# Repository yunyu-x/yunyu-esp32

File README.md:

# yunyu-esp32: 灵伴·悄悄 (LingBuddy) 物理具身智能伴侣与 ESP32 开源硬件套件

<div align="center">

**全栈独立、开箱即用的随身/桌面具身 AI 伴侣、微信小程序终端、Meta Muse Gadgets 生态与开源机器人硬件基座**  
*Full-Stack Independent Physical AI Voice Companion, WeChat Mini-Program Suite, Meta Muse Gadgets & Embedded Robotics*

[Release Notes v1.1.0](./docs/RELEASE_NOTES_v1.1.0.md) | [English](#english-summary) | [核心特性](#-核心特性-key-features) | [系统架构](#-系统架构-architecture) | [六大公理](#-不可违背的六大工程公理-the-6-constitutional-axioms) | [工程知识库](#-项目工程知识库-project-engineering-documentation) | [技能扩展](#-标准化技能扩展-standardized-skills) | [快速起步](#-快速起步-quick-start)

</div>

---

## 📖 项目简介 (Overview)

`yunyu-esp32` 是一个**完全独立自洽的物理具身 AI 伴侣与开源硬件生态工程**。本项目将前沿大语言模型与多模态情感计算深度融入嵌入式物理实体，构建了涵盖**嵌入式固件、微信小程序客户端、桌面 Web 伴侣、Meta Muse 具身代理接入、开源机器人机电控制及严格工程测试**的全栈闭环：

1. **灵伴·悄悄 (LingBuddy / Qiaoqiao) 嵌入式固件 (`firmware/m5sticks3_buddy`)**：
   运行在 M5Stack StickS3（ESP32-S3-PICO-1，8MB Flash + 8MB PSRAM）硬件底座上。内置离线声学唤醒词「悄悄」匹配引擎、阿里云百炼实时语音大模型全双工流式问答、正面按键 A 毫秒级物理打断（Barge-In）、12 种迪士尼拟态矢量微表情与 Tamagotchi 亲密度系统、8 轮长程记忆滑动压缩与 NVS 持久化、PSRAM 135×240 零撕裂双缓冲显存、异步 BLE 指令队列以及网络多态徽章。
2. **微信小程序端产品套件 (`wechat_miniprogram/`)**：
   秉持 Apple Human Interface Guidelines (HIG) 原生极简美学打造。涵盖 4 大核心 Tab（首页动态表情与心声、投喂互动中心、心声日记流、设置与配网面板）；支持蓝牙 BLE NUS 多包流式组包通讯、双通道配网（常规宽带 Wi-Fi 与手机共享移动热点自适应切换）、热点流量配额监控与超额自动熔断防护、DPR 自适应 `<avatar-canvas>` 动态微表情渲染、Taptic 触觉反馈震动以及离线优先本地存储。
3. **桌面与 Web 伴侣控制台 (`web/` & `scripts/`)**：
   提供基于 Web Bluetooth API 的隔空投喂中心 (`web/lingbuddy_companion.html`)、双向音频测试网关、以及两级语义向量检索记忆知识库 (`scripts/lingbuddy_vector_store.py`)。
4. **Meta Muse Gadgets 生态原生接入 (`external_repos/muse-gadget-sdk`, `include/muse_gadget_client.h`, Doc 31)**：
   深度研学并接入 Meta 官方开源的 Muse Gadgets 框架。通过 Noise_XX 全双工加密隧道和 Home Link 建立与云端 Muse Secure VM 的持久连接，支持 Push-to-Talk 24kHz 流式交互与本地具身 RPC 控制。
5. **开源机器人硬件扩展 (`microduck/` & `hardware/`)**：
   包含 MicroDuck 双足走路鸭机器人（基于 ESP32 的 CPG 步态引擎与舵机标定系统）、以及灵方微型机器人主控 PCBA v2.0（4层沉金 PCB、SPICE 多回路严苛仿真验证）。
6. **自动化工程测试与持续集成 (`tests/`)**：
   内置 100 项覆盖声学唤醒、音频防破音限幅、微表情动力学、BLE NUS 分包重组、热点配额熔断、驱动 Hub、硬件自测的自动化回归测试，100% 绿色通过。

---

## 🚀 核心特性 (Key Features)

### 1. 全双工大模型语音交互与离线唤醒
- **离线声学唤醒词「悄悄」**：基于板载 MEMS 硅麦 + ES8311 音频前端，毫秒级快速声学特征匹配，抗噪免疫；
- **阿里云百炼实时大模型 (DashScope Realtime WSS)**：16kHz 16-bit Mono PCM 双向双工流式传输，低延迟语音合成回放（AW8737 功放驱动）；
- **物理打断 (Barge-In)**：语音回放过程中随时按下正面按键 A，瞬时中断服务端合成与硬件回放，即刻重置拾音。

### 2. 迪士尼拟态微表情与情感动力学系统 (Tamagotchi Engine)
- **12 种拟态微表情**：涵盖开心、好奇、思考、眨眼、睡觉、惊讶、撒娇等细腻情感，具备凝视追踪与眨眼物理衰减阻尼；
- **Tamagotchi 亲密度系统**：记录投喂、抚摸与对话频次，数值随时间平滑演化，驱动微表情与交互心声动态进阶；
- **PSRAM 显存零撕裂双缓冲 (Axiom 3)**：开辟 135×240 @ 16-bit RGB565 精灵显存画布（仅占 64.8KB PSRAM），离线合成后经 SPI DMA 单次原子性推送，彻底根除 15Hz 物理闪烁与背光撕裂。

### 3. 跨端自适应通讯与双通道安全配网
- **BLE Nordic UART Service (NUS)**：广播合规 30 字节，特征值支持高速无应答写入；
- **双通道智能配网**：
  - **常规宽带 Wi-Fi 模式**：局域网高速通道，设备徽章亮绿底 **"WiFi"**；
  - **手机共享热点模式**：顶部与设备端徽章显示暖橙底 **"HOT"**，小程序实时统计已用流量 MB，支持配额设定与超额硬件级断网熔断保护；
  - **断网警示**：网络异常时设备显示亮红底 **"!NET"**。
- **防截断多包分片流 (Axiom 6)**：长文本与记忆 JSON 经自适应分片流传输，内置 `safeTruncateUtf8` 字符级边界保护器，杜绝非法字节导致的 WebSocket 1007 协议违规或解析异常。

### 4. Apple HIG 人文美学微信小程序
- **iOS 原生质感**：纯黑背景 (`#000000`)、层级卡片 (`#1C1C1E` / `#2C2C2E`)、SF Pro / PingFang 规范排版、0.5px 极细微边框；
- **四 Tab 完整产品布局**：首页微表情、隔空投喂甜品货架、Notes 风格心声随笔、iOS 设置分组配网；
- **微信上线保障**：内置离线仿真模式（Demo Mode）与硬件视频指引，轻松应对微信平台审核。

---

## 📐 系统架构 (Architecture)

```mermaid
flowchart TD
    subgraph Clients["调测与交互客户端 (Clients)"]
        WeChat["微信小程序 (WeChat Mini-Program)<br/>Apple HIG 美学 / 4-Tab / 热点流量监控"]
        WebDash["Web 蓝牙/局域网伴侣控制台<br/>隔空投喂 / 向量检索 / 音频调试"]
        MetaMuse["Meta Muse 代理大脑<br/>Muse Secure VM / Noise_XX Home Link"]
        Desktop["PC 桌面开发终端<br/>PlatformIO / 串口 COM3 诊断 / Pytest"]
    end

    subgraph StickS3["StickS3 物理伴侣 (代号「悄悄」) 核心中枢"]
        direction TB
        subgraph NetLayer["通信与协议解耦层 (Axiom 2 & 6)"]
            BLE_NUS["BLE NUS (0xFFB0)<br/>自旋锁 micro-queue 入队"]
            WiFi_Hotspot["双通道网络引擎<br/>宽带 WiFi / 手机热点 HOT / 流量熔断"]
            MuseClient["Meta Muse Gadget 客户端<br/>Noise_XX 隧道 / 串口 Hatch"]
            HttpServer["轻量级 REST API<br/>/api/pet/status /api/wifi/config"]
        end
        
        subgraph CoreTasks["FreeRTOS 核心任务调度"]
            LoopTask["主循环 loopTask (16KB+ 栈)<br/>StickS3BLESync::update() 消费指令"]
            AudioTask["双工音频任务 audioTask (6KB 栈)<br/>离线唤醒 + DashScope PCM 流"]
            AvatarTask["微表情与亲密度计算<br/>12 种拟态动作 + 物理水准仪"]
        end

        subgraph DisplaySub["显存渲染子系统 (Axiom 3)"]
            Canvas["PSRAM 双缓冲显存画布<br/>LGFX_Sprite (135x240 @ 16-bit RGB565)"]
            LCD["ST7789v2 1.14' 物理屏幕<br/>SPI DMA 单次原子推送 (零撕裂)"]
            Canvas -->|DMA Push| LCD
        end

        AudioSub["音频子系统 (PSRAM 320KB)<br/>MEMS 硅麦 + ES8311 + AW8737 功放"]
        MemoryStore["长程记忆引擎<br/>8 轮两级窗口压缩 + NVS 持久化"]
    end

    subgraph HardwareExt["具身与硬件扩展 (Embodied Hardware)"]
        MicroDuck["MicroDuck 双足走路鸭机器人<br/>ESP32 CPG 步态引擎 / 舵机校准"]
        LingCube["灵方微型机器人主控 PCBA v2.0<br/>4层沉金板 / DRV8833 / EPM 磁吸"]
    end

    WeChat -->|BLE NUS 0xFFB4 / 手机热点| BLE_NUS
    WebDash -->|Web Bluetooth / HTTP| BLE_NUS
    WebDash -->|Wi-Fi SoftAP / HTTP 80| HttpServer
    MetaMuse -->|Home Link / HTTP RPC| MuseClient
    Desktop -->|串口 COM3 / 烧录| StickS3

    NetLayer -->|微栈入队| CoreTasks
    CoreTasks --> DisplaySub
    CoreTasks <--> AudioSub
    CoreTasks <--> MemoryStore

    StickS3 -.->|HIL 步态遥控| MicroDuck
    StickS3 -.->|HIL 地面调测| LingCube
```

---

## ⚖️ 不可违背的六大工程公理 (The 6 Constitutional Axioms)

依据 [`docs/30_PROJECT_AXIOMS_AND_HANDOVER.md`](./docs/30_PROJECT_AXIOMS_AND_HANDOVER.md)，在 `yunyu-esp32` 的持续演进中，**以下六大公理为不可违背的最高工程基石**：

1. **【公理一：真实硬件烧录验证公理】(Strict Hardware Verification Law)**  
   固件改动绝不能停留在“代码编写完成”或“本地编译通过”，必须经由 PlatformIO 烧录至真实连接的物理硬件（`COM3`），触发 RTS/DTR 硬件级硬重启，实测阅读 10~15 秒串口日志确认自检全项通过。
2. **【公理二：中断与通讯协议栈异步解耦公理】(Interrupt & Protocol Task Decoupling Law)**  
   在 ESP-IDF 底层任务（特别是堆栈仅 3KB 的 `BTC_TASK`）中严禁执行 NVS 读写、Wi-Fi 切换或阻塞计算；所有下发指令仅在自旋锁临界区向微栈队列入队，并在拥有 16KB+ 栈空间的 `loopTask` 中异步消费。
3. **【公理三：显存零撕裂双缓冲物理公理】(Zero-Tear Double-Buffering Law)**  
   杜绝物理屏直写清屏。必须利用 8MB PSRAM 开辟 135×240 精灵画布（`LGFX_Sprite`），所有汉字、微表情与水准仪在显存中无缝合成后经 SPI DMA 单次原子推送，彻底消除频闪。
4. **【公理四：网络模式显式区分与端到端一致性公理】(Explicit Network Mode & Coherence Law)**  
   严格区分手机热点（橙色 "HOT" / 流量监控看板与熔断保护）与常规宽带（绿色 "WiFi"），断网亮红底 "!NET"；小程序主页与设置页数据源 100% 一致。
5. **【公理五：零功能回退与渐进加固公理】(Non-Regression & Progressive Hardening Law)**  
   任何新增功能不得导致已有基线特性（离线唤醒词「悄悄」、阿里百炼流式语音、按键打断、12种微表情、8轮记忆压缩、I2C互斥锁）发生任何劣化。
6. **【公理六：跨端自适应协议与防截断编码公理】(Adaptive Multi-Chunk & Robust Encoding Law)**  
   跨端通信长文本必须支持多包分片流与接收端组包拼帧；文本截断必须使用字符级算法（`safeTruncateUtf8`），严禁跨字节撕裂导致解析崩溃或 WebSocket 1007 协议违规。

---

## ⚡ 硬件定义与引脚映射 (Pinout Specifications)

### M5Stack StickS3 板载核心外设映射

| 外设模块 | 核心芯片 / 组件 | ESP32-S3 GPIO 引脚 | 驱动方式与通信协议 | 说明 |
| :--- | :--- | :--- | :--- | :--- |
| **电源门控** | M5PM1 PMIC | I2C (SDA: G10, SCL: G9) | I2C Addr `0x6E` | GPIO2: LCD 3.3V, GPIO3: 功放使能 |
| **正面按键 A** | 主功能实体按键 | **GPIO 11** | 内部上拉输入 | 语音物理打断 (Barge-In) / 录音触发 |
| **侧面按键 B** | 辅助控制实体按键 | **GPIO 12** | 内部上拉输入 | 页面轮换与辅助功能切换 |
| **彩色屏幕** | ST7789v2 1.14" LCD | SPI3 (SCLK: G17, MOSI: G18, DC: G15, CS: G14, RST: G21) | SPI (27MHz DMA) | 135 × 240 分辨率，PSRAM 双缓冲显存 |
| **6轴姿态计** | Bosch BMI270 | I2C (SDA: G10, SCL: G9) | I2C Addr `0x69` | 姿态角感应与动态水准球平衡算法 |
| **音频前端** | ES8311 + AW8737 PA | I2S0 (LRCK: G7, BCLK: G8, DOUT: G6, DIN: G5) | I2S (16kHz 16bit Mono) | 板载 MEMS 硅麦采集 + 喇叭流式回放 |
| **外扩动力接口** | Grove 4-Pin 接口 | GPIO 1 / GPIO 2, 5V, GND | M5PM1 门控 5V | 外接 MicroDuck 舵机或机器人 HIL 调测 |

---

## 📚 项目工程知识库 (Project Engineering Documentation)

本项目建立了完备、专业的技术文档体系，全部文档归档于 [`docs/`](./docs/)：

| 专案分类 | 文档名称与索引 | 核心论证与工程规范 |
| :--- | :--- | :--- |
| **最高工程基石** | [**30_PROJECT_AXIOMS_AND_HANDOVER.md**](./docs/30_PROJECT_AXIOMS_AND_HANDOVER.md) | 六大不可违背工程公理、实机监控基线、全套工具链验证命令与会话交接指南 |
| **提示词标准库** | [**AGENT_CONTINUATION_PROMPTS.md**](./docs/AGENT_CONTINUATION_PROMPTS.md) | 跨生命周期 AI Agent 通用母版、细分研发方向（审批终端/地面台/菜单）提示词模板 |
| **微信小程序端** | [**28_M5StickS3微信小程序对接架构与通信协议工程指南.md**](./docs/28_M5StickS3微信小程序对接架构与通信协议工程指南.md)<br/>[**29_微信小程序与移动端研发交接指南_HANDOVER_MOBILE.md**](./docs/29_微信小程序与移动端研发交接指南_HANDOVER_MOBILE.md) | 小程序 4-Tab 完整架构、BLE NUS 分包重组、热点配额监控熔断、上线审核攻略 |
| **Meta Muse 接入** | [**31_Meta_Muse_Gadgets微型自重构机器人与物理伴侣全栈接入方案与工程实施详案.md**](./docs/31_Meta_Muse_Gadgets微型自重构机器人与物理伴侣全栈接入方案与工程实施详案.md) | Meta 2026-10-02 开源 `muse-gadget-sdk` 研学、Noise_XX 隧道、具身技能标准与实施详案 |
| **伴侣与表情架构** | [**27_基于MuseCharm哲学的M5StickS3灵宠伴侣软硬件架构与工程论证大案.md**](./docs/27_基于MuseCharm哲学的M5StickS3灵宠伴侣软硬件架构与工程论证大案.md)<br/>[**27_StickS3物理伴侣全流程对话开发实录与教学手册.md**](./docs/27_StickS3物理伴侣全流程对话开发实录与教学手册.md) | 迪士尼微表情动力学、Tamagotchi 亲密度系统、长程记忆压缩与对话实录教程 |
| **硬件与调测基线** | [**01_StickS3_Hardware_and_Bringup_Guide.md**](./docs/01_StickS3_Hardware_and_Bringup_Guide.md)<br/>[**03_StickS3_Three_Schemes_Verification.md**](./docs/03_StickS3_Three_Schemes_Verification.md)<br/>[**25_M5Stack_StickS3物理伴侣与地面调测终端开发全流程及三方案验证详案.md**](./docs/25_M5Stack_StickS3物理伴侣与地面调测终端开发全流程及三方案验证详案.md) | M5StickS3 硬件上电流程、三大方案（M5Burner / PlatformIO / Claude Buddy）全面验证 |
| **双向语音与资源** | [**HANDOVER_VOICE_DIALOGUE_AND_RESOURCE_MANAGEMENT.md**](./docs/HANDOVER_VOICE_DIALOGUE_AND_RESOURCE_MANAGEMENT.md)<br/>[**RELEASE_NOTES_v1.0.0.md**](./docs/RELEASE_NOTES_v1.0.0.md) | 百炼实时语音流、双向音频协议、内存防溢出与 v1.0.0 稳定生产基线发布记录 |

---

## 🛠️ 标准化技能扩展 (Standardized Skills)

项目所有专属专业技能均统一梳理并保存在根目录 `skills/` 下，已配置 `.agents/skills.json` 支持 Antigravity 全自动化识别与调度：

1. **[skills/lingbuddy-firmware-ops/](./skills/lingbuddy-firmware-ops/SKILL.md)**：  
   StickS3 嵌入式固件编译、极速烧录（`COM3`）、硬重启检验与六大公理违规审计技能；
2. **[skills/wechat-miniprogram-companion/](./skills/wechat-miniprogram-companion/SKILL.md)**：  
   微信小程序伴侣研发、Apple HIG 视觉规范审查、BLE NUS 多包通信协议、双通道配网与发布上线技能；
3. **[skills/muse-gadget-companion/](./skills/muse-gadget-companion/SKILL.md)**：  
   Meta Muse Gadgets 接入与具身技能管理（Noise_XX 隧道、Home Link 穿透、Push-to-Talk 24kHz 流）；
4. **[skills/public-service-tunnel/](./skills/public-service-tunnel/SKILL.md)**：  
   本地伴侣控制台与 Web 预览在线穿透管理技能（ngrok、Cloudflare Quick Tunnel 自适应容灾切换）；
5. **[skills/document-content-verifier/](./skills/document-content-verifier/SKILL.md)**：  
   第一性原理与公理化文档内容交叉复核技能（自然科学公理、量纲齐次性、多模态交付）；
6. **[skills/open-source-repo-analyzer/](./skills/open-source-repo-analyzer/SKILL.md)**：  
   自主开源项目研学、AST 源码分析与跨项目接口适配器生成技能；
7. **[skills/pcb-design-verifier/](./skills/pcb-design-verifier/SKILL.md)**：  
   KiCad 原理图/PCB 审查与多回路 SPICE 瞬态电路仿真技能；
8. **[skills/gadget-lingcube-msrr/](./skills/gadget-lingcube-msrr/SKILL.md)** & **[skills/gadget-lingmatrix-sim/](./skills/gadget-lingmatrix-sim/SKILL.md)**：  
   Meta Muse 具身物理机器人控制与数字孪生仿真技能。

---

## 🛠️ 快速起步 (Quick Start)

### 1. 环境准备与依赖安装
```bash
# 1. 安装 Python 核心依赖 (包含 platformio, pytest, bleak, numpy 等)
pip install -r requirements.txt

# 2. 安装小程序端构建依赖 (若需运行微信开发者工具自动化)
npm install
```

### 2. 固件编译与真实硬件烧录 (践行公理一)
```bash
# 本地编译固件
python -m platformio run -e m5sticks3_buddy

# 烧录固件至物理硬件 (本地串口 COM3)
python -m platformio run -e m5sticks3_buddy -t upload

# 触发 RTS/DTR 硬件级硬重启并读取实时串口自检日志 (运行 10~15 秒)
python -c "import serial, time; ser = serial.Serial('COM3', 115200, timeout=1); ser.setDTR(False); ser.setRTS(True); time.sleep(0.1); ser.setRTS(False); time.sleep(0.2); start = time.time(); [print(ser.readline().decode('utf-8', errors='replace').strip()) for _ in iter(lambda: ser.readline() if time.time()-start < 10 else None, None)]; ser.close()"
```

### 3. 执行全套 100 项自动化回归测试
```bash
pytest tests/ -v
```
*(100 项声学唤醒、百炼双工、音频防破音限幅、微表情动力学、BLE多包拼帧、热点配额熔断、驱动 Hub、硬件自测全部通过)*

### 4. 微信小程序开发与预览
1. 打开**微信开发者工具**；
2. 导入项目目录：`D:\workspace\code\yunyu-esp32\wechat_miniprogram`；
3. 输入测试 AppID 或使用已有的小程序账号；
4. 即可在模拟器中体验暗黑 Apple HIG 美学界面、4 大 Tab、微表情渲染与仿真交互模式；连接真实 StickS3 时自动开启 BLE NUS 双向通信。

### 5. 桌面 Web 蓝牙伴侣与向量知识库
```bash
# 启动本地伴侣控制台 Web 服务
python scripts/lingbuddy_companion.py
# 浏览器访问: http://127.0.0.1:8000 (支持 Chrome / Edge Web Bluetooth 直连)

# 启动向量记忆知识库查询
python scripts/lingbuddy_vector_store.py
```

---

## 📂 仓库目录结构 (Directory Structure)

```
yunyu-esp32/
├── .agents/                       # Antigravity Agent 技能索引配置 (skills.json)
├── .github/                       # GitHub Actions CI 流水线
├── docs/                          # 项目最高公理、工程交接、提示词库与全套技术详案 (Docs 01~31)
├── firmware/
│   └── m5sticks3_buddy/           # StickS3 物理伴侣与双模地面调测台工程 (PlatformIO)
│       ├── include/               # 离线唤醒、音频驱动、微表情、BLE同步、百炼Client、MuseClient
│       ├── src/                   # main.cpp, sticks3_hal.cpp, buddy_protocol.cpp
│       └── platformio.ini         # PlatformIO 编译构建配置
├── wechat_miniprogram/            # 微信小程序端 4-Tab 完整产品套件
│   ├── pages/                     # index (首页), feed (投喂), diary (日记), settings (设置配网)
│   ├── components/avatar-canvas/  # DPR 自适应矢量微表情渲染组件
│   ├── utils/                     # BLE 通信、Wi-Fi/热点管理、触觉反馈、离线存储、加密防护
│   └── assets/tabbar/             # 苹果暗黑高保真 TabBar 图标资产
├── web/
│   └── lingbuddy_companion.html   # Web Bluetooth / Wi-Fi 隔空投喂伴侣控制台
├── external_repos/
│   └── muse-gadget-sdk/           # Meta Muse Gadgets 官方开源硬件与通信 SDK
├── microduck/                     # MicroDuck 双足走路鸭机器人机电步态工程
├── hardware/                      # 灵方微型机器人主控 PCBA v2.0 与硬件设计资产
├── scripts/                       # 自动化点亮代理、向量检索、对话压测、音频自测脚本
├── skills/                        # 8 项标准化 Antigravity 专属技能扩展
├── tests/                         # 100 项全自动化回归测试套件 (Pytest)
├── package.json                   # 小程序与前端构建工具链配置
├── pyproject.toml                 # 现代化 Python 包元数据与 pytest 配置
├── requirements.txt               # Python 运行与构建依赖
├── CONTRIBUTING.md                # 代码贡献与工程准则
├── LICENSE                        # Apache License 2.0 开源协议
└── README.md                      # 本文档
```

---

## 📄 开源许可证 (License)

本项目遵循 [Apache License 2.0](./LICENSE) 协议开源。软件源码、固件代码、微信小程序套件及硬件工程设计均保障商业友好与学术研究自由。

---

<div id="english-summary">

### English Summary

`yunyu-esp32` is a fully decoupled, standalone open-source physical AI voice companion and embodied robotics hardware ecosystem.

**Core Highlights**:
- **LingBuddy (悄悄) Companion Firmware**: Running on M5Stack StickS3 (ESP32-S3), featuring offline acoustic wakeword "悄悄", Alibaba Bailian DashScope Realtime full-duplex voice streaming, physical button barge-in, 12 Disney-inspired parametric avatar emotions, Tamagotchi intimacy engine, 8-turn long-horizon memory compaction, zero-tear PSRAM double-buffering (Axiom 3), and async spinlock BLE queue (Axiom 2).
- **WeChat Mini-Program Product Suite**: Built with Apple Human Interface Guidelines (HIG) aesthetic, offering 4 primary tabs (Avatar & Thoughts, Feeding Center, Heartfelt Diary, and Network Settings), BLE Nordic UART Service multi-chunk streaming, dual-channel network provisioning (broadband Wi-Fi + mobile hotspot with quota cutoff protection), DPR-aware `<avatar-canvas>`, and haptic feedback.
- **Meta Muse Gadgets Ecosystem Integration**: Native compliance with Meta's open-source Muse Gadget SDK, supporting Noise_XX encrypted Home Link tunneling, Push-to-Talk 24kHz audio, and embodied robotics skill dispatching.
- **MicroDuck Bipedal Robotics**: CPG locomotion gait controller, servo calibration, and hardware kinematics.
- **6 Constitutional Axioms**: Strict adherence to hardware-verified releases, task decoupling, anti-flicker double-buffering, network coherence, non-regression, and safe Unicode-boundary encoding.

</div>

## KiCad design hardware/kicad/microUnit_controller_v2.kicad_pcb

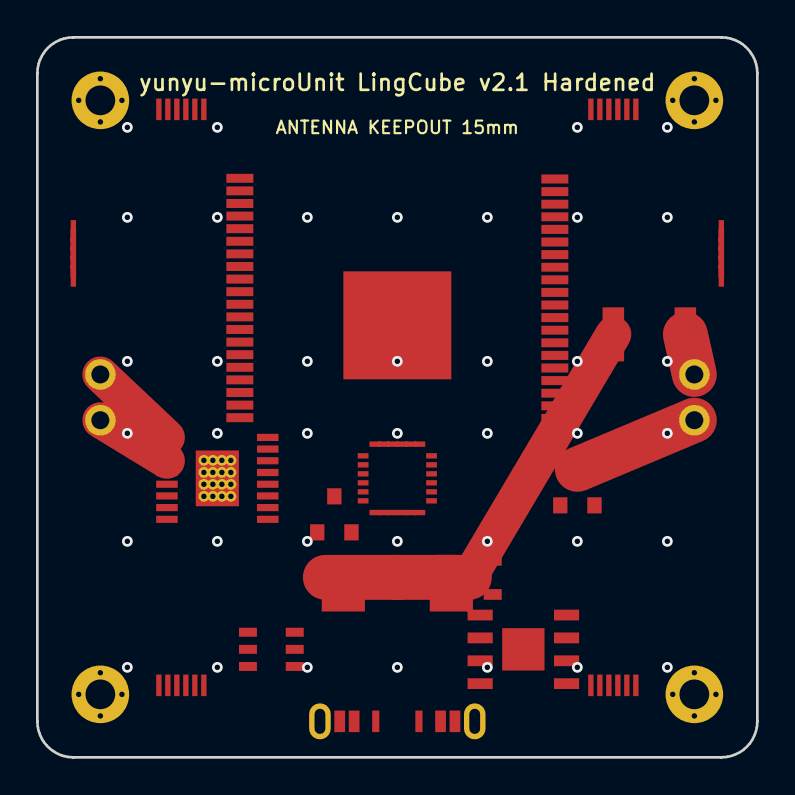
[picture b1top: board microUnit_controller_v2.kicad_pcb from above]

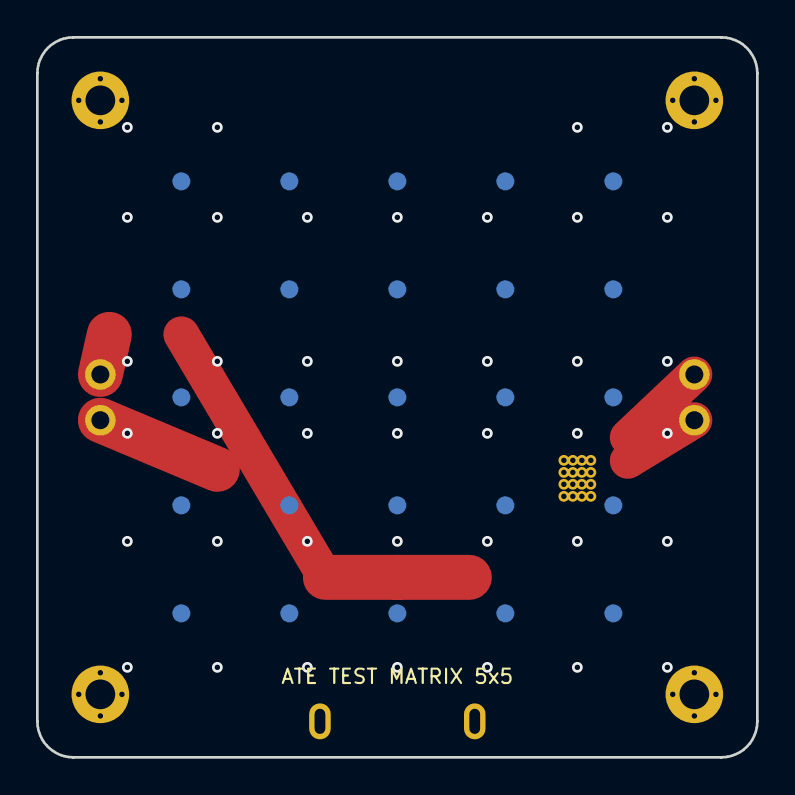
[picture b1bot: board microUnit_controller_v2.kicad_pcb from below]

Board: 4 copper layers, 40.0 x 40.0 mm, 48 parts (25 on the bottom side), 15 nets.

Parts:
C1: 470uF POSCAP; CP_EIA-7343-31_Kemet-D
F1: 1812L150PR_1.5A; Fuse_1812_4532Metric
H1, H2, H3, H4: M1.6_GND_MOUNT; MountingHole_1.65mm_M1.6_Pad_ViaStitched
J2: MOTOR_OUT; PinHeader_1x02_P2.54mm_Vertical
J3: EPM_COIL_OUT; PinHeader_1x02_P2.54mm_Vertical
J4: FPC_FACE_POS_X; Hirose_FH12-6S-0.5SH_1x06-1MP_P0.50mm_Horizontal
J5: FPC_FACE_NEG_X; Hirose_FH12-6S-0.5SH_1x06-1MP_P0.50mm_Horizontal
J6: FPC_FACE_POS_Y; Hirose_FH12-6S-0.5SH_1x06-1MP_P0.50mm_Horizontal
J7: FPC_FACE_NEG_Y; Hirose_FH12-6S-0.5SH_1x06-1MP_P0.50mm_Horizontal
J8: FPC_FACE_POS_Z; Hirose_FH12-6S-0.5SH_1x06-1MP_P0.50mm_Horizontal
J9: FPC_FACE_NEG_Z; Hirose_FH12-6S-0.5SH_1x06-1MP_P0.50mm_Horizontal
J_USB: TYPE-C-16P; USB_C_Receptacle_GCT_USB4105-xx-A_16P_TopMnt_Horizontal
Q1: AO3400A; SOT-23
Q4: AO3401A_IMU_SW; SOT-23
TP1: TP_VBAT_CELL; TestPoint_Pad_D1.0mm_OD1.6mm
TP2: TP_VBAT_SW; TestPoint_Pad_D1.0mm_OD1.6mm
TP3: TP_VCC_3V3; TestPoint_Pad_D1.0mm_OD1.6mm
TP4: TP_GND; TestPoint_Pad_D1.0mm_OD1.6mm
TP5: TP_VBUS_5V; TestPoint_Pad_D1.0mm_OD1.6mm
TP6: TP_EN; TestPoint_Pad_D1.0mm_OD1.6mm
TP7: TP_BOOT; TestPoint_Pad_D1.0mm_OD1.6mm
TP8: TP_U0TXD; TestPoint_Pad_D1.0mm_OD1.6mm
TP9: TP_U0RXD; TestPoint_Pad_D1.0mm_OD1.6mm
TP10: TP_I2C_SDA; TestPoint_Pad_D1.0mm_OD1.6mm
TP11: TP_I2C_SCL; TestPoint_Pad_D1.0mm_OD1.6mm
TP12: TP_MOTOR_PWM_A; TestPoint_Pad_D1.0mm_OD1.6mm
TP13: TP_MOTOR_PWM_B; TestPoint_Pad_D1.0mm_OD1.6mm
TP14: TP_MOTOR_OUT1; TestPoint_Pad_D1.0mm_OD1.6mm
TP15: TP_MOTOR_OUT2; TestPoint_Pad_D1.0mm_OD1.6mm
TP16: TP_DRV_FAULT; TestPoint_Pad_D1.0mm_OD1.6mm
TP17: TP_EPM_PULSE_TRIG; TestPoint_Pad_D1.0mm_OD1.6mm
TP18: TP_EPM_DRAIN; TestPoint_Pad_D1.0mm_OD1.6mm
TP19: TP_TP4056_CHRG; TestPoint_Pad_D1.0mm_OD1.6mm
TP20: TP_TP4056_STDBY; TestPoint_Pad_D1.0mm_OD1.6mm
TP21: TP_DW01A_OD; TestPoint_Pad_D1.0mm_OD1.6mm
TP22: TP_DW01A_OC; TestPoint_Pad_D1.0mm_OD1.6mm
TP23: TP_IR_TX; TestPoint_Pad_D1.0mm_OD1.6mm
TP24: TP_IR_RX; TestPoint_Pad_D1.0mm_OD1.6mm
TP25: TP_IMU_INT; TestPoint_Pad_D1.0mm_OD1.6mm
U1: ESP32-S3-WROOM-1-N8R8; ESP32-S3-WROOM-1
U2: DRV8833PWP; HTSSOP-16-1EP_4.4x5mm_P0.65mm_EP3.4x5mm_Mask2.4x3.1mm_Therm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
U3: SGM2205-3.3; SOT-23-5
U4: MPU-6050; InvenSense_QFN-24_4x4mm_P0.5mm
U5: TP4056; SOIC-8-1EP_3.9x4.9mm_P1.27mm_EP2.35x2.35mm
U6: DW01A; SOT-23-6

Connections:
DW01A_OC: TP22.1, U6.3
DW01A_OD: TP21.1, U6.1
EPM_DRAIN: J3.2, Q1.3, TP18.1
EPM_VBAT_PROT: F1.2, J3.1
GND: C1.2, H1.1, H2.1, H3.1, H4.1, J4.3, J5.3, J6.3, J7.3, J8.3, J9.3, J_USB.A1, J_USB.B1, J_USB.S1, J_USB.S2, Q1.2, TP4.1, U1.1, U1.20, U1.40, U1.41, U2.6, U2.8, U2.17, U3.2, U4.1, U4.9, U4.11, U4.18, U5.1, U5.3, U5.9, U6.6
IMU_PWR_EN: Q4.1, U1.21
IMU_VDD_SW: Q4.3, U4.8, U4.13
MOTOR_OUT1: J2.1, TP14.1, U2.2
MOTOR_OUT2: J2.2, TP15.1, U2.4
MOTOR_PWM_A: TP12.1, U2.16
MOTOR_PWM_B: TP13.1, U2.15
VBAT: F1.1, J4.1, J5.1, J6.1, J7.1, J8.1, J9.1, TP2.1, U2.14, U3.1, U3.3
VBAT_CELL_POS: TP1.1, U5.5
VBUS: J_USB.A4, J_USB.B4, TP5.1, U5.4, U5.8
VCC_3V3: C1.1, J4.2, J5.2, J6.2, J7.2, J8.2, J9.2, Q4.2, TP3.1, U1.2, U2.1, U3.5

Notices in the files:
README.md:
License: Apache 2.0
